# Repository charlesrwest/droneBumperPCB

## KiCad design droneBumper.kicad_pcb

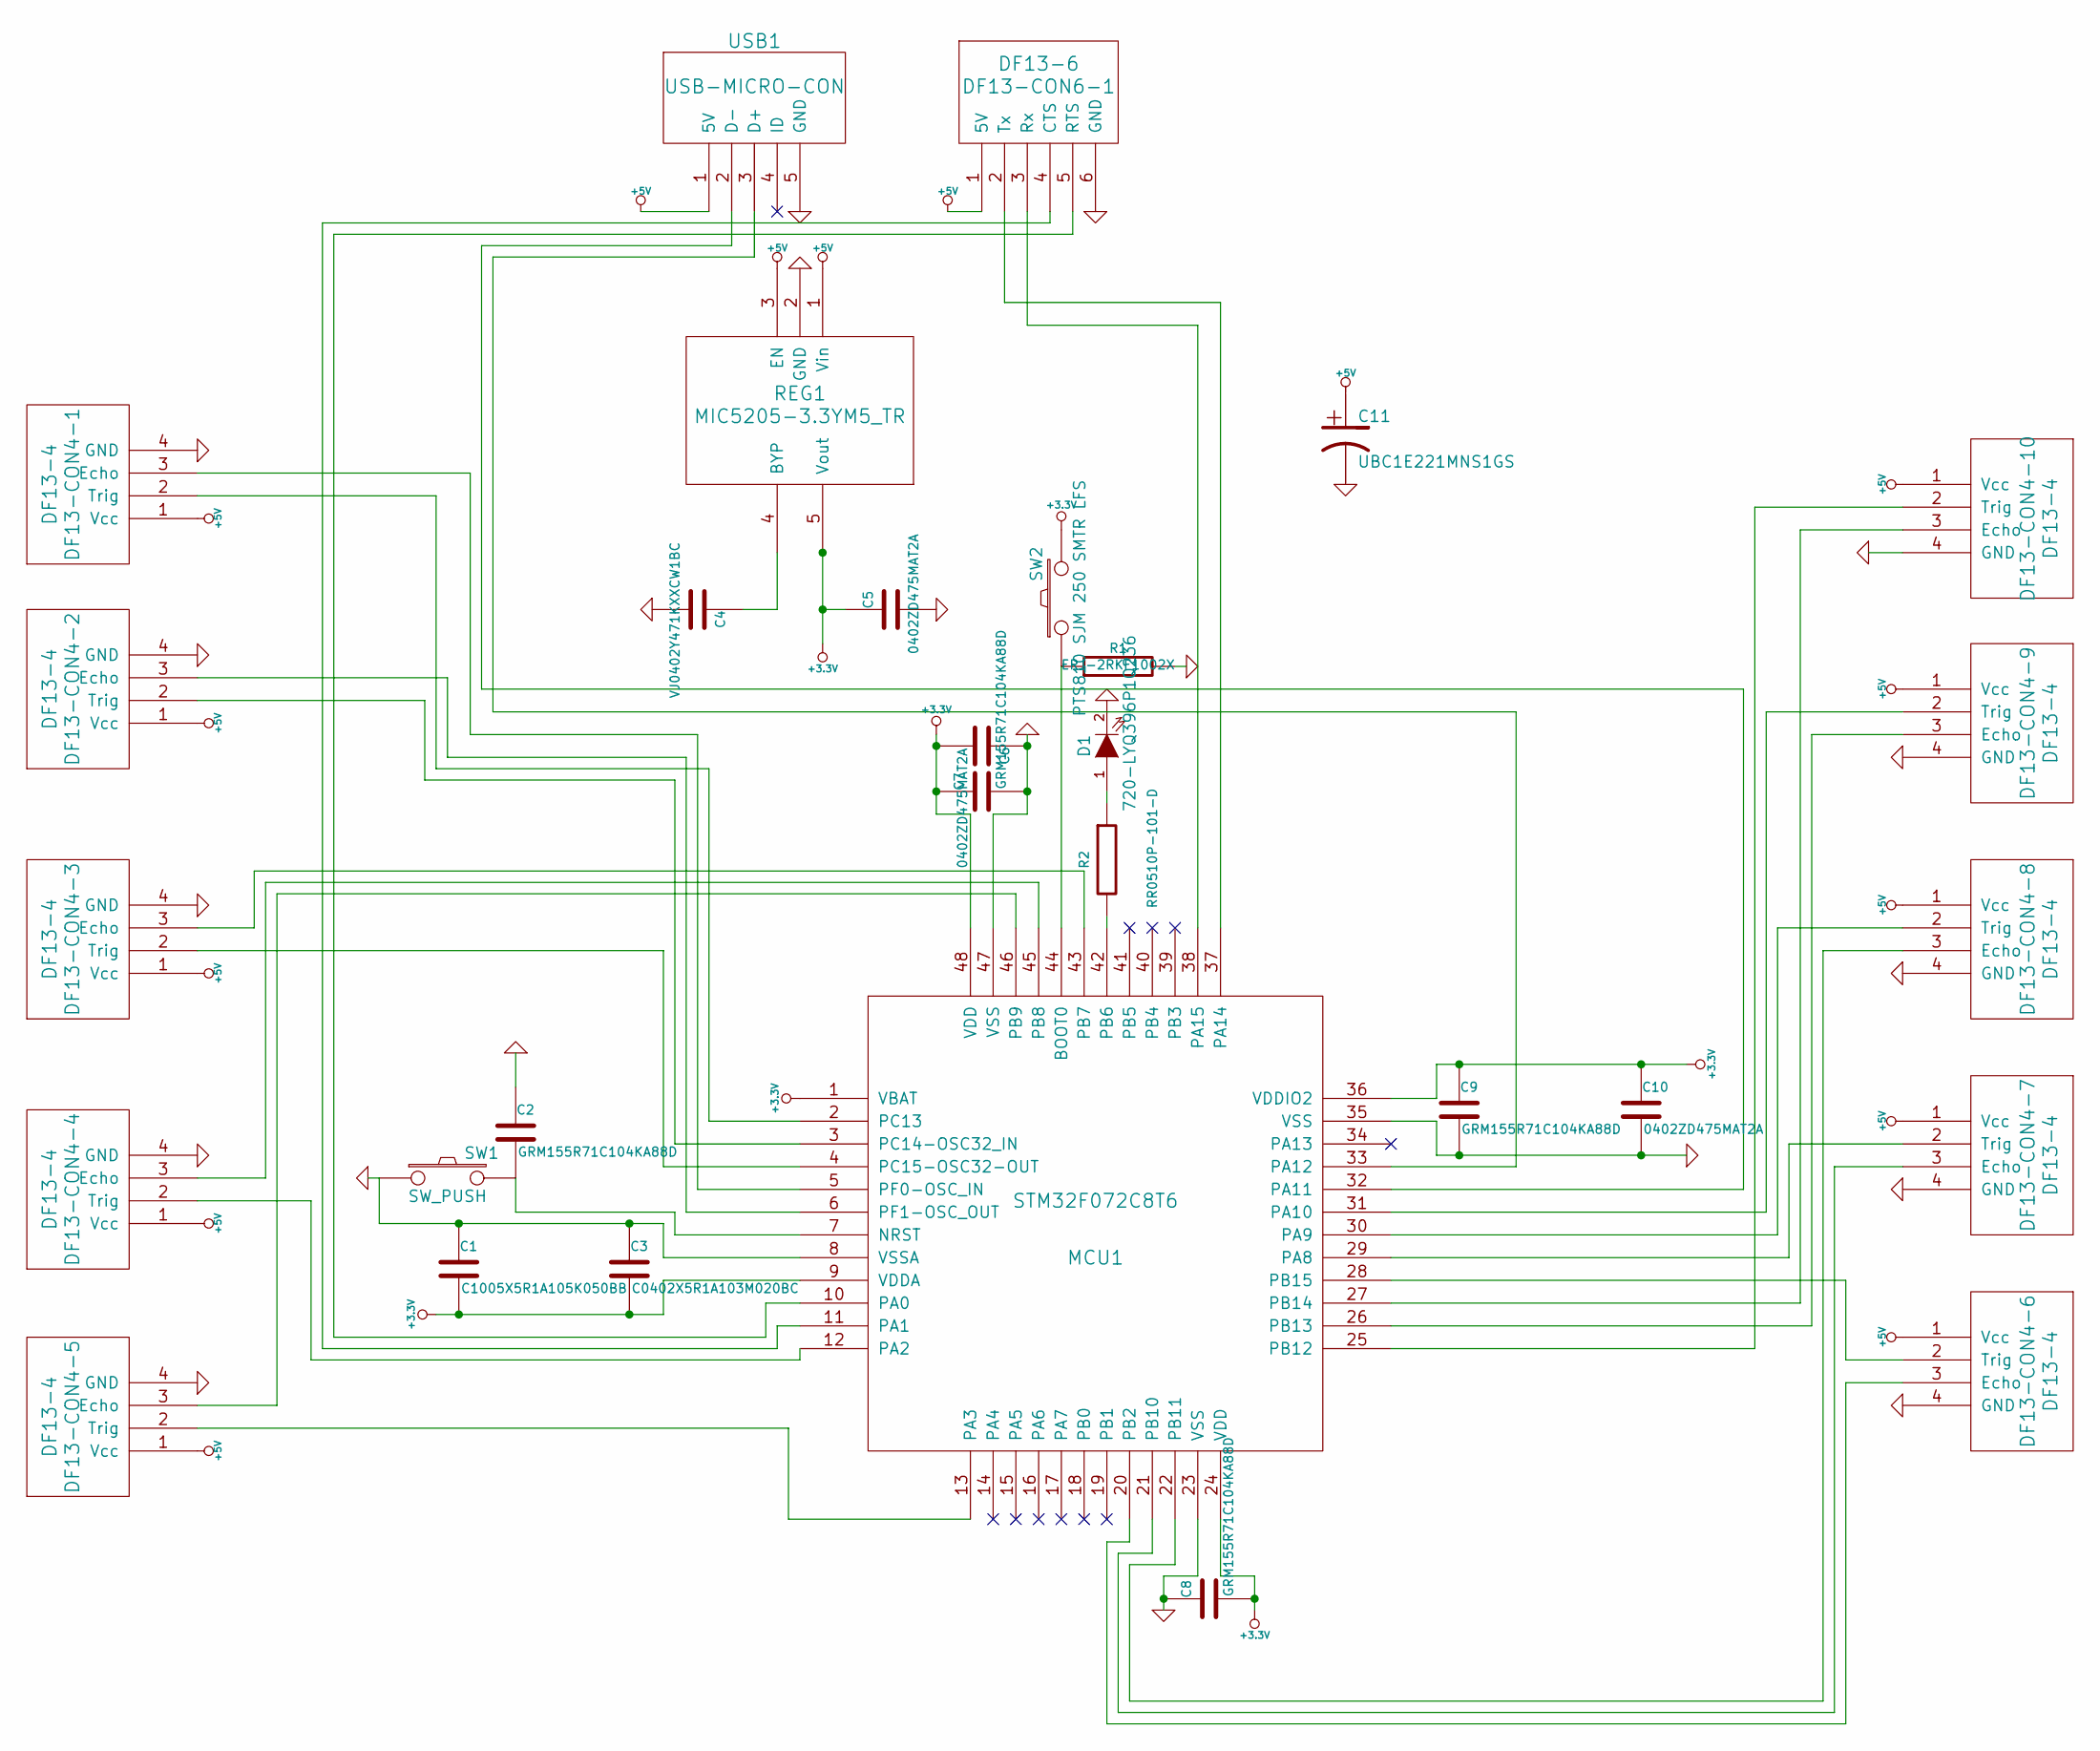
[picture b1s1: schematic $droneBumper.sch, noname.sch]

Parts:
C1: C1005X5R1A105K050BB
C2, C7, C8, C9: GRM155R71C104KA88D
C3: C0402X5R1A103M020BC
C4: VJ0402Y471KXXCW1BC
C5, C6, C10: 0402ZD475MAT2A
C11: UBC1E221MNS1GS
D1: 720-LYQ396P1Q236
DF13-CON4-1, DF13-CON4-2, DF13-CON4-3, DF13-CON4-4, DF13-CON4-5, DF13-CON4-6, DF13-CON4-7, DF13-CON4-8, DF13-CON4-9, DF13-CON4-10: DF13-4
DF13-CON6-1: DF13-6
MCU1: STM32F072C8T6
R1: ERJ-2RKF1002X
R2: RR0510P-101-D
REG1: MIC5205-3.3YM5_TR
SW1: SW_PUSH
SW2: PTS810 SJM 250 SMTR LFS
USB1: USB-MICRO-CON

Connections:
+3.3V: C1.2, C3.2, C5.1, C6.2, C7.1, C8.2, C9.1, C10.1, MCU1.1 (VBAT), MCU1.9 (VDDA), MCU1.24 (VDD), MCU1.36 (VDDIO2), MCU1.48 (VDD), REG1.5 (Vout), SW2.2
+5V: C11.1, DF13-CON4-1.1 (Vcc), DF13-CON4-2.1 (Vcc), DF13-CON4-3.1 (Vcc), DF13-CON4-4.1 (Vcc), DF13-CON4-5.1 (Vcc), DF13-CON4-6.1 (Vcc), DF13-CON4-7.1 (Vcc), DF13-CON4-8.1 (Vcc), DF13-CON4-9.1 (Vcc), DF13-CON4-10.1 (Vcc), DF13-CON6-1.1 (5V), REG1.1 (Vin), REG1.3 (EN), USB1.1 (5V)
GND: C1.1, C2.1, C3.1, C4.2, C5.2, C6.1, C7.2, C8.1, C9.2, C10.2, C11.2, D1.2 (K), DF13-CON4-1.4 (GND), DF13-CON4-2.4 (GND), DF13-CON4-3.4 (GND), DF13-CON4-4.4 (GND), DF13-CON4-5.4 (GND), DF13-CON4-6.4 (GND), DF13-CON4-7.4 (GND), DF13-CON4-8.4 (GND), DF13-CON4-9.4 (GND), DF13-CON4-10.4 (GND), DF13-CON6-1.6 (GND), MCU1.8 (VSSA), MCU1.23 (VSS), MCU1.35 (VSS), MCU1.47 (VSS), R1.2, REG1.2 (GND), SW1.1, USB1.5 (GND)
unnamed: DF13-CON4-7.3 (Echo), MCU1.21 (PB10)
unnamed: DF13-CON4-10.3 (Echo), MCU1.27 (PB14)
unnamed: DF13-CON4-9.3 (Echo), MCU1.26 (PB13)
unnamed: DF13-CON4-8.3 (Echo), MCU1.22 (PB11)
unnamed: DF13-CON4-6.3 (Echo), MCU1.20 (PB2)
unnamed: DF13-CON4-5.3 (Echo), MCU1.46 (PB9)
unnamed: DF13-CON4-3.2 (Trig), MCU1.4 (PC15-OSC32-OUT)
unnamed: DF13-CON4-7.2 (Trig), MCU1.29 (PA8)
unnamed: DF13-CON4-6.2 (Trig), MCU1.28 (PB15)
unnamed: DF13-CON4-5.2 (Trig), MCU1.13 (PA3)
unnamed: DF13-CON4-4.2 (Trig), MCU1.12 (PA2)
unnamed: DF13-CON4-2.2 (Trig), MCU1.3 (PC14-OSC32_IN)
unnamed: DF13-CON4-1.2 (Trig), MCU1.2 (PC13)
unnamed: DF13-CON4-2.3 (Echo), MCU1.6 (PF1-OSC_OUT)
unnamed: DF13-CON4-1.3 (Echo), MCU1.5 (PF0-OSC_IN)
unnamed: DF13-CON6-1.4 (CTS), MCU1.11 (PA1)
unnamed: DF13-CON6-1.2 (Tx), MCU1.37 (PA14)
unnamed: DF13-CON4-4.3 (Echo), MCU1.45 (PB8)
unnamed: DF13-CON4-3.3 (Echo), MCU1.43 (PB7)
unnamed: DF13-CON6-1.5 (RTS), MCU1.10 (PA0)
unnamed: MCU1.32 (PA11), USB1.2 (D-)
unnamed: DF13-CON6-1.3 (Rx), MCU1.38 (PA15)
unnamed: D1.1 (A), R2.1
unnamed: MCU1.42 (PB6), R2.2
unnamed: DF13-CON4-10.2 (Trig), MCU1.25 (PB12)
unnamed: DF13-CON4-9.2 (Trig), MCU1.31 (PA10)
unnamed: DF13-CON4-8.2 (Trig), MCU1.30 (PA9)
unnamed: C4.1, REG1.4 (BYP)
unnamed: C2.2, MCU1.7 (NRST), SW1.2
unnamed: MCU1.44 (BOOT0), R1.1, SW2.1
unnamed: MCU1.33 (PA12), USB1.3 (D+)

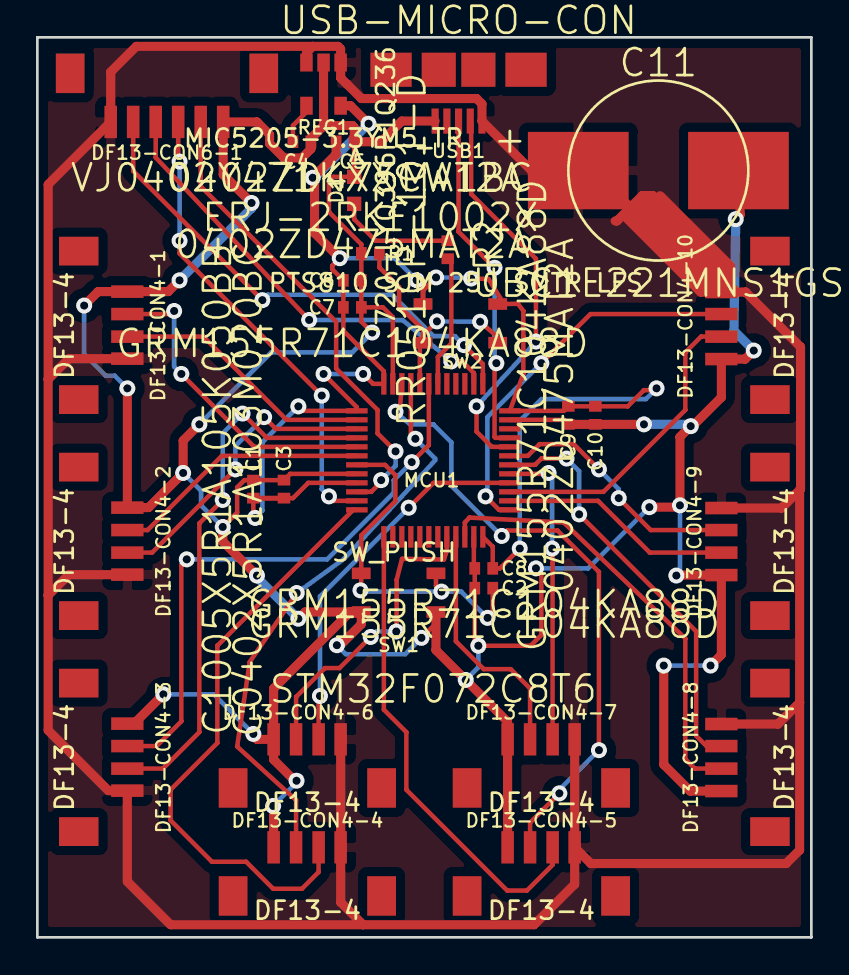
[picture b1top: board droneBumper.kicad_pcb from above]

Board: 2 copper layers, 43.0 x 50.0 mm, 30 parts (0 on the bottom side), 34 nets.

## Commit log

2015-09-07 Made project a git repository. Starting at revision 3.
2015-09-07 Oops. Make that revision 2. Also, generated gerber files.
2015-09-07 Saved.
2015-09-15 Added gerbers.
2015-09-20 Some small changes. Still need to change ordering of pins on USART.
